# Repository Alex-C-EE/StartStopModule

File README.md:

# StartStopModule
A repo containing original and custom start stop modules for robo sumo and their firmware. Manufacturing files generated.

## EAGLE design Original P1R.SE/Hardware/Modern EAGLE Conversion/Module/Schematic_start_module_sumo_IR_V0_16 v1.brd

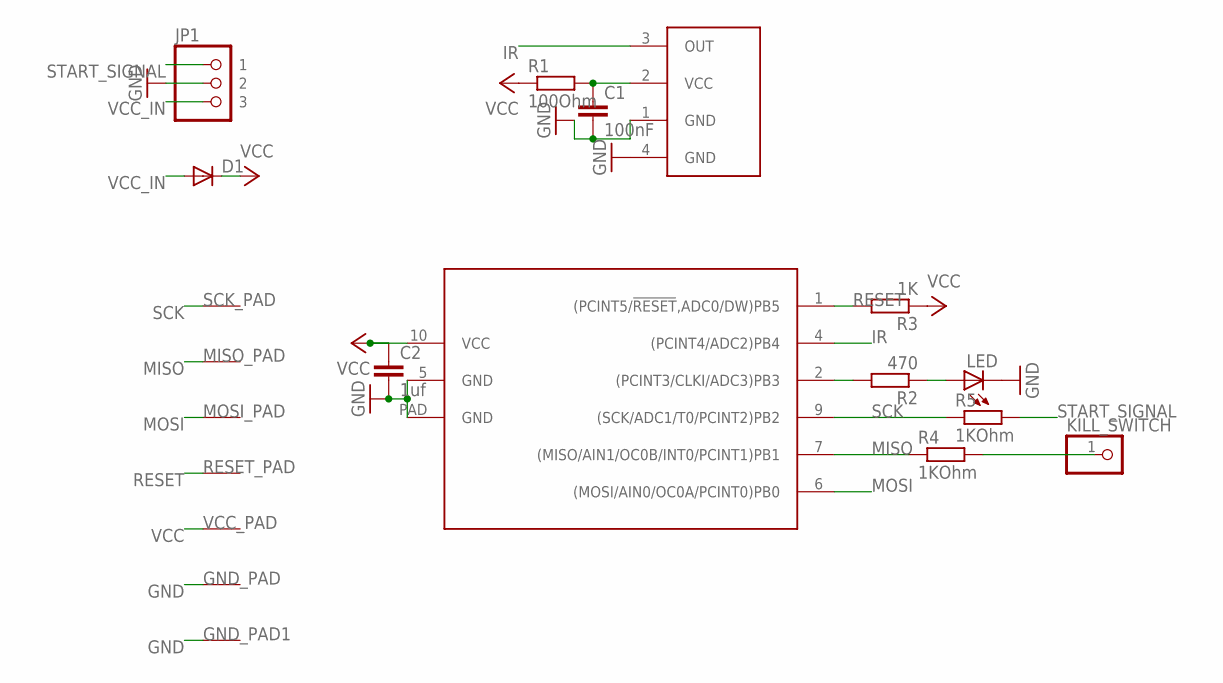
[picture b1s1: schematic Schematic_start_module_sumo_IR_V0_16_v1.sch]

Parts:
C1: 100nF; C0603
C2: 1uf; C0603
D1: DIODE-SOD523; SOD523
GND_PAD: PAD50X50; PAD_50X50
GND_PAD1: PAD75X75; PAD_75X75
IR1: TSOP77338TS; TSOP77338
JP1: PINHD-1X3PIN; 1X3
KILL_SWITCH: PINHD-1X1; 1X01
LED: LED0603; 0603_SMALL
MISO_PAD: PAD50X50; PAD_50X50
MOSI_PAD: mosi; PAD_75X75
R1: 100Ohm; R0603
R2: 470; R0603
R3: 1K; R0603
R4, R5: 1KOhm; R0603
RESET_PAD: PAD50X50; PAD_50X50
SCK_PAD: PAD50X50; PAD_50X50
UC: ATTINY13A; DFN10
VCC_PAD: PAD50X50; PAD_50X50

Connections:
GND: C1.2, C2.2, GND_PAD.P$1, GND_PAD1.P$1, IR1.1 (GND), IR1.4 (GND), JP1.2, LED.2 (C), UC.5 (GND), UC.PAD (GND)
IR: IR1.3 (OUT), UC.4 ((PCINT4/ADC2)PB4)
KILL_SWITCH: KILL_SWITCH.1, R4.2
MISO: MISO_PAD.P$1, R4.1, UC.7 ((MISO/AIN1/OC0B/INT0/PCINT1)PB1)
MOSI: MOSI_PAD.P$1, UC.6 ((MOSI/AIN0/OC0A/PCINT0)PB0)
unnamed: R2.2, UC.2 ((PCINT3/CLKI/ADC3)PB3)
unnamed: LED.1 (A), R2.1
unnamed: C1.1, IR1.2 (VCC), R1.2
RESET: R3.2, RESET_PAD.P$1, UC.1 ((PCINT5/!RESET,ADC0/DW)PB5)
SCK: R5.1, SCK_PAD.P$1, UC.9 ((SCK/ADC1/T0/PCINT2)PB2)
START_SIGNAL: JP1.1, R5.2
VCC: C2.1, D1.C, R1.1, R3.1, UC.10 (VCC), VCC_PAD.P$1
VCC_IN: D1.A, JP1.3

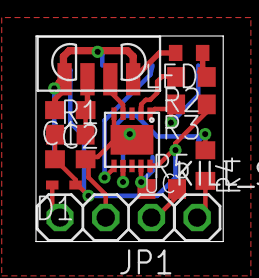
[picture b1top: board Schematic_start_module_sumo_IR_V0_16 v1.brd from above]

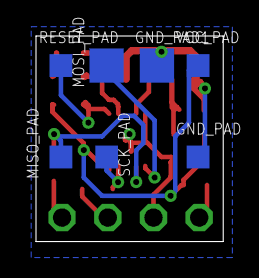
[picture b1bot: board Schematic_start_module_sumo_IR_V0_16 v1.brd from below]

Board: 2 copper layers, 10.4 x 11.4 mm, 20 parts (7 on the bottom side), 13 nets.

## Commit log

2025-11-10 Start Good
2025-12-12 Inverted SWDIO/SWCLK to correct pins.
